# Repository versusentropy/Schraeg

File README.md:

# Schräg

Schräg is an 8HP multimode filter module for the eurorack format, based off the [Bastl Cinnamon](https://bastl-instruments.com/eurorack/modules/cinnamon).

## Smaller Warning and Disclaimer

As of 2021-03-01, at least one person has reported successfully building the current board revision. However, another builder reported a minor issue with the attenuverter circuits which prevents full-range voltage control over resonance (and limits voltage control over FM). This should be fixable only with component substitutions, we’re working on a fix. More information and updates [in the corresponding lines thread](https://llllllll.co/t/diy-module-release-schrag-bastl-cinnamon-rework/40590).

See the Changelog below for more updates and version-specific fixes.

## Quick links

* [Schematic](Schraeg/Schraeg.pdf)
* [Gerbers](Schraeg/output)
* [BOM](Schraeg/Schraeg%20BOM.csv)
* [Schräg on ModularGrid](https://www.modulargrid.net/e/other-unknown-schraeg)

## Features

Schräg is effectively a repackaged Bastl Cinnamon:

* Multimode filter with independent outputs (2-pole LP, 2-pole HP, 1-pole BP)
* V/oct input
* Self-resonates for use as a sine oscillator
* Input with an attenuator and 5x gain switch
* Two character switches for altering the resonance tracking
* All-SMD construction in a DIY-friendly format, with 0603 handsoldering footprints, all components on the back of the circuit board
* Built mostly using standard and easily-available components

with a few modifications:

* larger 8HP form factor, allowing for a big juicy cutoff knob and larger character and gain switches
* Voltage control over resonance, through an attenuverter
* FM input through an attenuverter, which works as a pitch fine-tune control with nothing patched
* A bi-directional power connector, with polyfuses
* An Interactive BOM (`Schraeg/Output/Interactive BOM.html` once you’ve cloned the repo locally) to aid in part placement
* Schematics and PCB laid out using KiCAD

The additional functionality is achieved with a minimum of extra components, thanks to the two unused VCA cells in the original design.

## License

The schematic, board layout and graphics are released under a cc-by-sa license. [Bastl Instruments](https://bastl-instruments.com/) generously gave their permission for me to release my rework of their module. They’re a cool company. Go check out their work!

## Development

In 2019 I was looking through the [Bastl Cinnamon schematic](https://github.com/bastl-instruments/bastlSchematics/blob/master/CINNAMON_V1.2.pdf) and realised that it only uses two of the four available V2164D VCA cells.

At the time I needed PCB layout practise (and a filter module for my DIY eurorack!), so I ended up prototyping and building an 8HP version of cinnamon for myself which uses the two spare cells to implement voltage control over resonance, as well as a few other little additions listed above.

I called it “Schräg” because of both the angled panel design, the weird sounds possible with Bastl’s cool distortion circuits, and the strange way KiCAD mangled the panel graphics.

A bit more than a year after building the first Schräg, I finally got around to fixing the various small issues with the first board revision, and asking Bastl if they were okay with me open-sourcing the project. They were, and here we are.

## Changelog

### v0.2.2

* Fixed attenuverter circuits (versusentroppy)
* Removed panel
* Added part numbers for JLCPCB
* Added placeholder for JLC's order number

### v0.2.1

* Fixed the LM4040 schematic symbols and PCB traces (#2)

### v0.2

* First version released to the public.
* These boards have an issue with the LM4040 orientation (see #2). Depending on the specific LM4040s, it may not cause any problems, but if building from scratch it’s best to install them correctly the first time. To fix it, solder the LM4040s at an angle so that pin 2 (NC) gets connected to pin 3 (5V Ref or GND, depending on the LM4040)

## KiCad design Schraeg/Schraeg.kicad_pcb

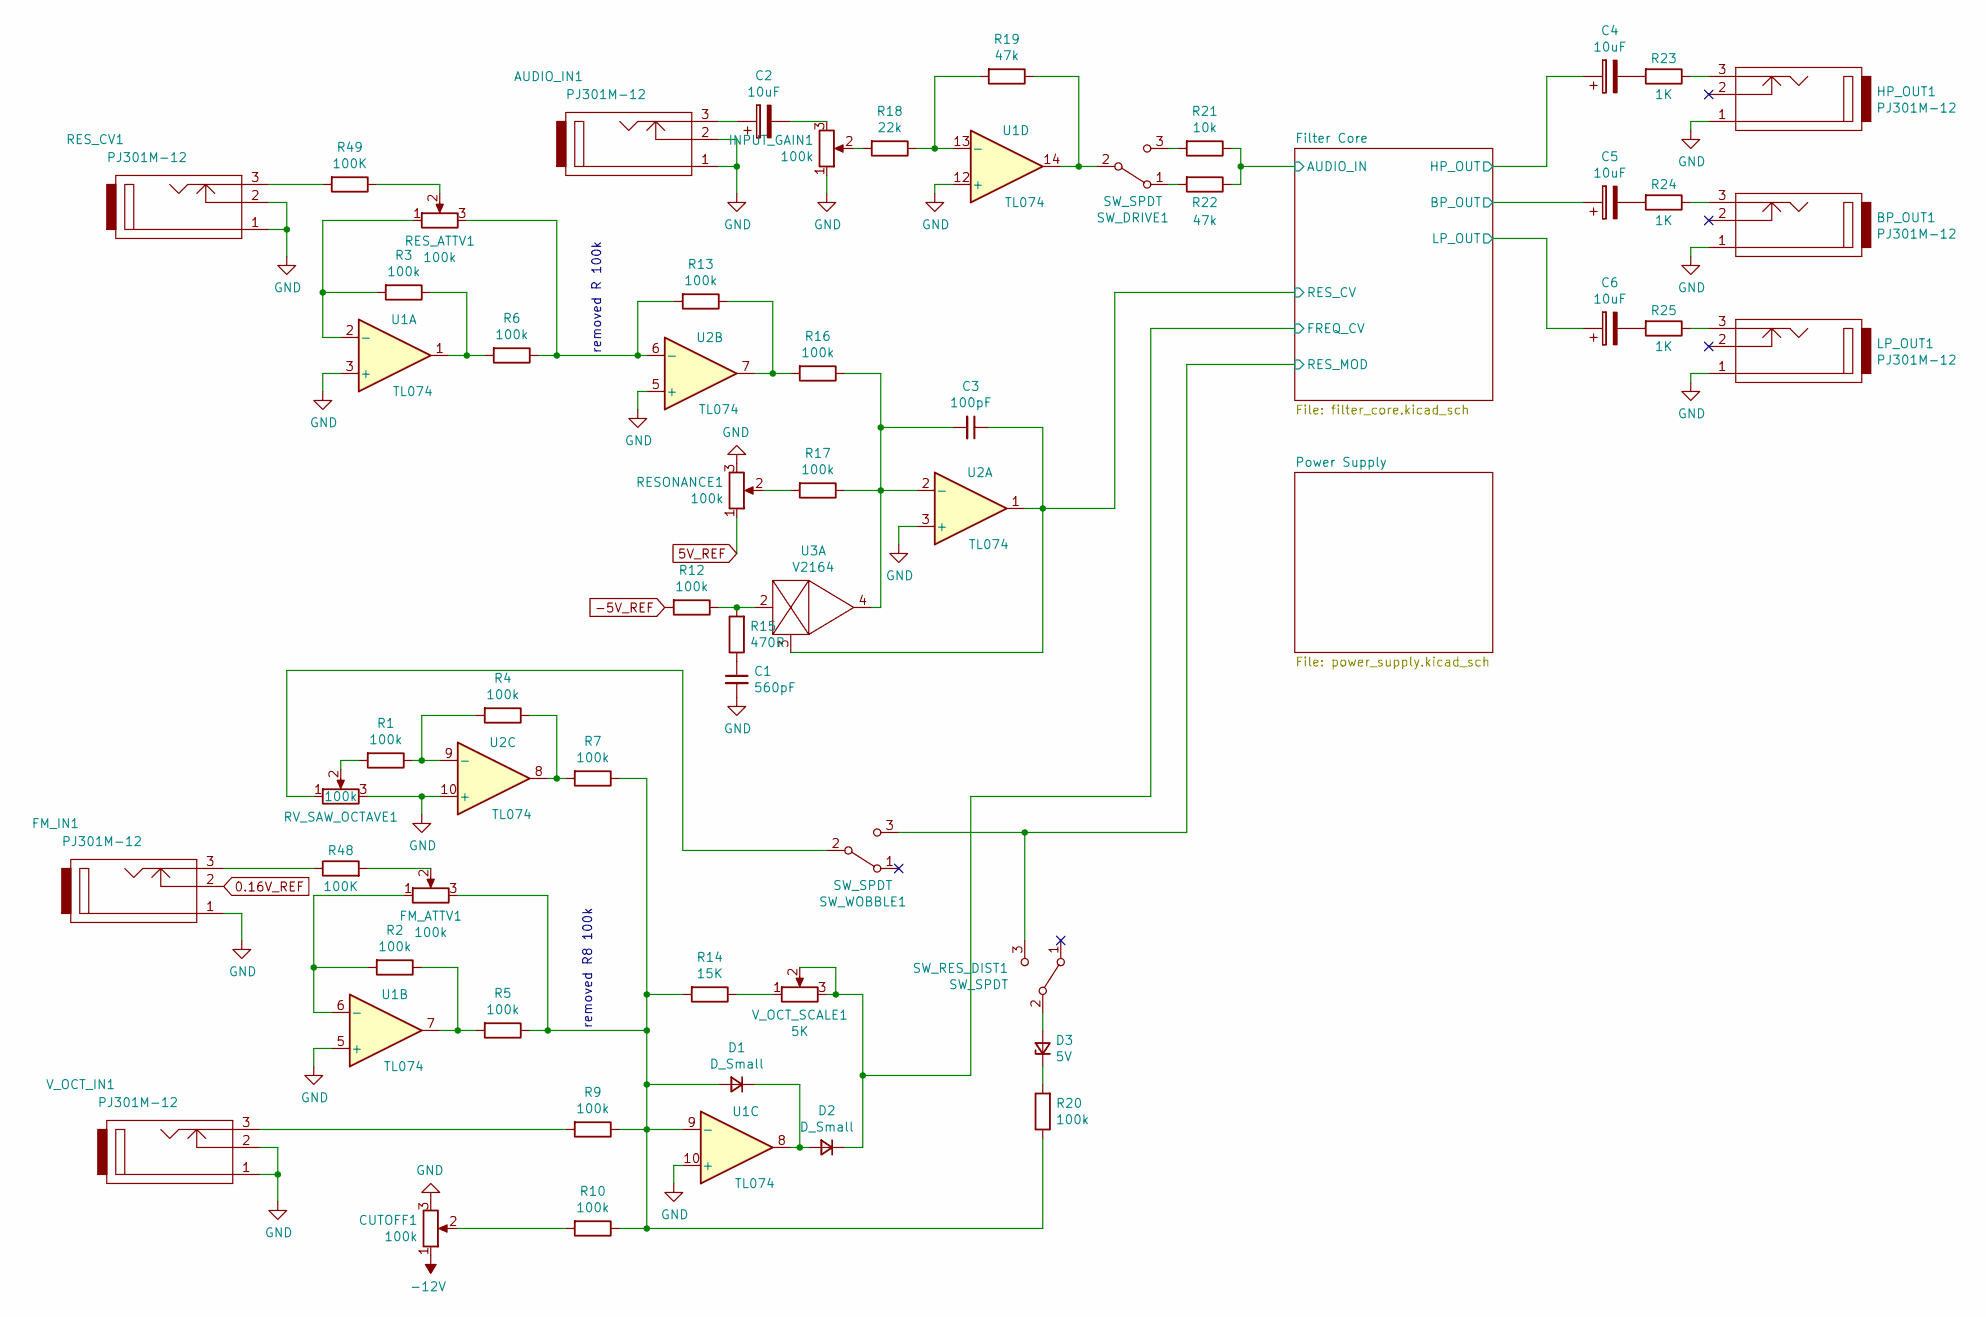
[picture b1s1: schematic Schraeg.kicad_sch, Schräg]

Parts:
AUDIO_IN1: PJ301M-12
BP_OUT1: PJ301M-12
C1: 560pF; C_0603_1608Metric_Pad1.05x0.95mm_HandSolder; LCSC C55393
C2, C4, C5, C6: 10uF; CP_Elec_5x4.5; Mouser 647-UCQ1V100MCL1GB
C3: 100pF; C_0603_1608Metric_Pad1.05x0.95mm_HandSolder; LCSC C14858
CUTOFF1: 100k; Alpha9mmPot
D1, D2: D_Small; D_SOD-123; LCSC C117948
D3: 5V; D_SOD-123; LCSC C173407
FM_ATTV1: 100k; Alpha9mmPot
FM_IN1: PJ301M-12
HP_OUT1: PJ301M-12
INPUT_GAIN1: 100k; Alpha9mmPot
LP_OUT1: PJ301M-12
R1, R2, R3, R4, R5, R6, R7, R9, R10, R12, R13, R16, R17, R20: 100k; R_0603_1608Metric_Pad1.05x0.95mm_HandSolder; LCSC C25803
R14: 15K; R_0603_1608Metric_Pad1.05x0.95mm_HandSolder; LCSC C22809
R15: 470R; R_0603_1608Metric_Pad1.05x0.95mm_HandSolder; LCSC C23179
R18: 22k; R_0603_1608Metric_Pad1.05x0.95mm_HandSolder; LCSC C31850
R19, R22: 47k; R_0603_1608Metric_Pad1.05x0.95mm_HandSolder; LCSC C25819
R21: 10k; R_0603_1608Metric_Pad1.05x0.95mm_HandSolder; LCSC C25804
R23, R24, R25: 1K; R_0603_1608Metric_Pad1.05x0.95mm_HandSolder; LCSC C21190
R48, R49: 100K; R_0603_1608Metric_Pad1.05x0.95mm_HandSolder; LCSC C25803
RESONANCE1: 100k; Alpha9mmPot
RES_ATTV1: 100k; Alpha9mmPot
RES_CV1: PJ301M-12
RV_SAW_OCTAVE1: 100k; Potentiometer_Bourns_3296W_Vertical
SW_DRIVE1: SW_SPDT; PinHeader_1x03_P2.54mm_Vertical
SW_RES_DIST1: SW_SPDT; PinHeader_1x03_P2.54mm_Vertical
SW_WOBBLE1: SW_SPDT; PinHeader_1x03_P2.54mm_Vertical
U1, U2: TL074; SOIC-14_3.9x8.7mm_P1.27mm; LCSC C12594
U3: V2164; SOIC-16_3.9x9.9mm_P1.27mm
V_OCT_IN1: PJ301M-12
V_OCT_SCALE1: 5K; Potentiometer_Bourns_3296W_Vertical

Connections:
0.16V_REF: FM_IN1.2; also elsewhere on the board
5V_REF: RESONANCE1.1; also elsewhere on the board
-5V_REF: R12.2; also elsewhere on the board
-12V: CUTOFF1.1; also elsewhere on the board
/Filter Core/AUDIO_IN: R21.1, R22.1; also elsewhere on the board
/Filter Core/BP_OUT: C5.1; also elsewhere on the board
/Filter Core/FREQ_CV: D2.1 (K), V_OCT_SCALE1.2, V_OCT_SCALE1.3; also elsewhere on the board
/Filter Core/HP_OUT: C4.1; also elsewhere on the board
/Filter Core/LP_OUT: C6.1; also elsewhere on the board
/Filter Core/RES_CV: C3.1, U2.1, U3.3; also elsewhere on the board
/Filter Core/RES_MOD: SW_RES_DIST1.3 (C), SW_WOBBLE1.3 (C); also elsewhere on the board
GND: AUDIO_IN1.1, AUDIO_IN1.2, BP_OUT1.1, C1.2, CUTOFF1.3, FM_IN1.1, HP_OUT1.1, INPUT_GAIN1.1, LP_OUT1.1, RESONANCE1.3, RES_CV1.1, RES_CV1.2, RV_SAW_OCTAVE1.3, U1.3 (+), U1.5 (+), U1.10 (+), U1.12 (+), U2.3 (+), U2.5 (+), U2.10 (+), V_OCT_IN1.1, V_OCT_IN1.2; also elsewhere on the board
unnamed: AUDIO_IN1.3, C2.1
unnamed: BP_OUT1.3, R24.1
unnamed: C1.1, R15.1
unnamed: C2.2, INPUT_GAIN1.3
unnamed: C3.2, R16.1, R17.1, U2.2 (-), U3.4
unnamed: C4.2, R23.2
unnamed: C5.2, R24.2
unnamed: C6.2, R25.2
unnamed: CUTOFF1.2, R10.2
unnamed: D1.1 (K), D2.2 (A), U1.8
unnamed: D1.2 (A), FM_ATTV1.3, R5.1, R7.1, R9.1, R10.1, R14.2, R20.1, U1.9 (-)
unnamed: D3.1 (K), R20.2
unnamed: D3.2 (A), SW_RES_DIST1.2 (B)
unnamed: FM_ATTV1.1, R2.2, U1.6 (-)
unnamed: FM_ATTV1.2, R48.2
unnamed: FM_IN1.3, R48.1
unnamed: HP_OUT1.3, R23.1
unnamed: INPUT_GAIN1.2, R18.2
unnamed: LP_OUT1.3, R25.1
unnamed: R1.1, R4.2, U2.9 (-)
unnamed: R1.2, RV_SAW_OCTAVE1.2
unnamed: R2.1, R5.2, U1.7
unnamed: R3.1, R6.2, U1.1
unnamed: R3.2, RES_ATTV1.1, U1.2 (-)
unnamed: R4.1, R7.2, U2.8
unnamed: R9.2, V_OCT_IN1.3
unnamed: R12.1, R15.2, U3.2
unnamed: R13.1, R16.2, U2.7
unnamed: R6.1, R13.2, RES_ATTV1.3, U2.6 (-)
unnamed: R14.1, V_OCT_SCALE1.1
unnamed: R17.2, RESONANCE1.2
unnamed: R18.1, R19.2, U1.13 (-)
unnamed: R19.1, SW_DRIVE1.2 (B), U1.14
unnamed: R21.2, SW_DRIVE1.3 (C)
unnamed: R22.2, SW_DRIVE1.1 (A)
unnamed: R49.1, RES_ATTV1.2
unnamed: R49.2, RES_CV1.3
unnamed: RV_SAW_OCTAVE1.1, SW_WOBBLE1.2 (B)

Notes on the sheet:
removed R8 100k
removed R 100k

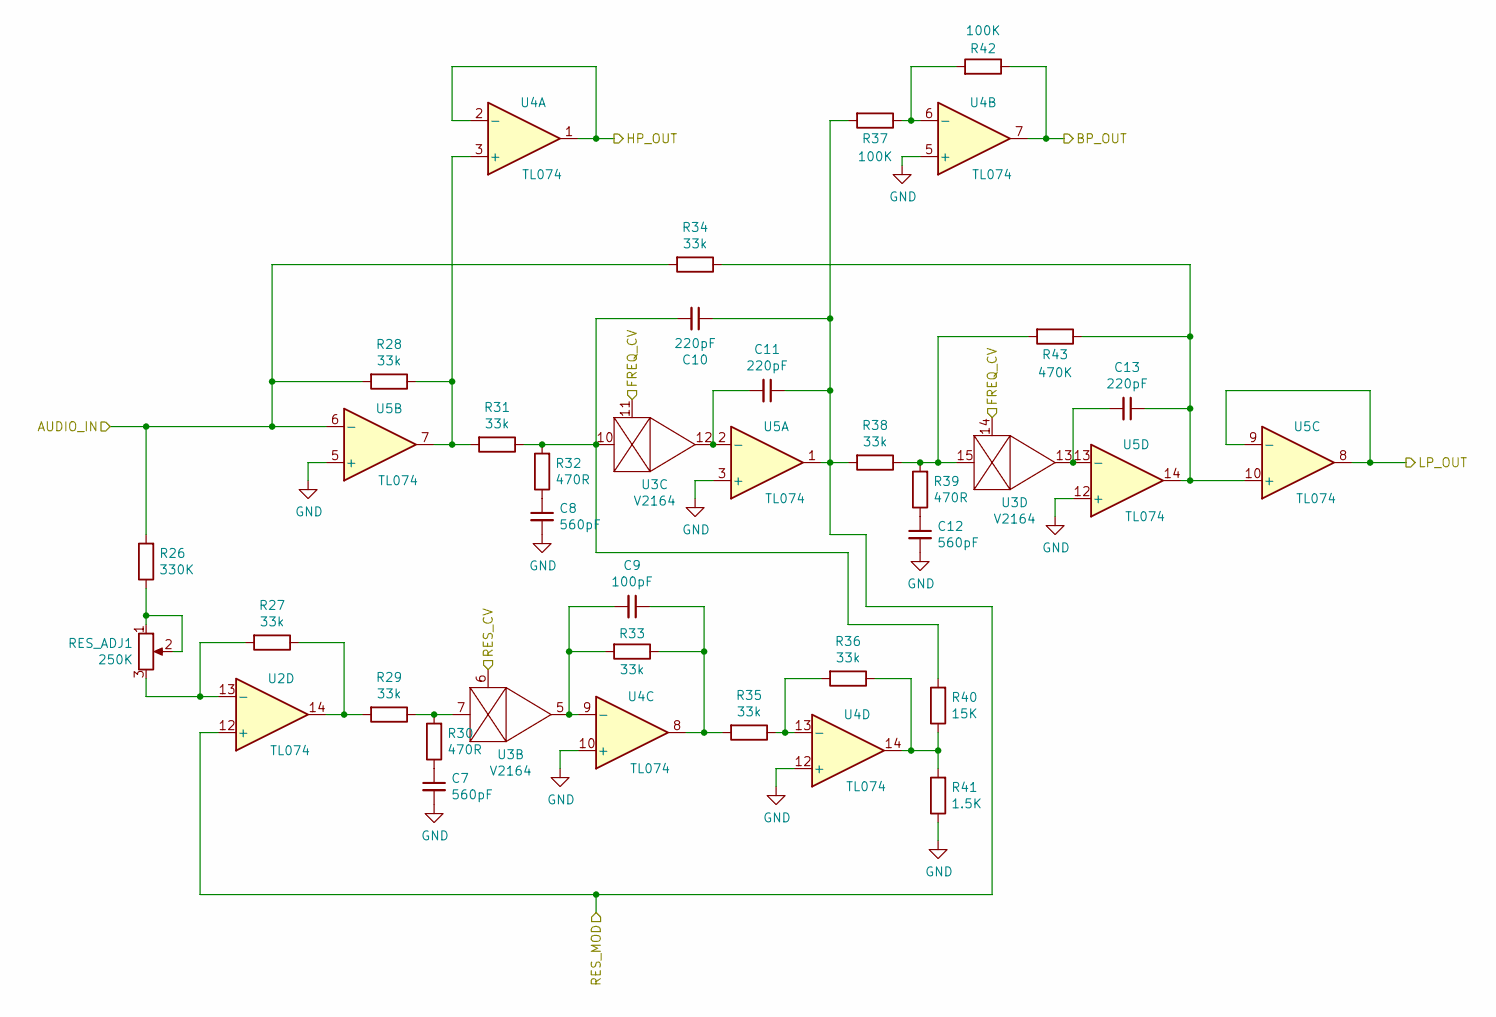
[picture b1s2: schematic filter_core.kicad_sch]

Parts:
C7, C8, C12: 560pF; C_0603_1608Metric_Pad1.05x0.95mm_HandSolder; LCSC C55393
C9: 100pF; C_0603_1608Metric_Pad1.05x0.95mm_HandSolder; LCSC C14858
C10, C11, C13: 220pF; C_0603_1608Metric_Pad1.05x0.95mm_HandSolder; LCSC C27675
R26: 330K; R_0603_1608Metric_Pad1.05x0.95mm_HandSolder; LCSC C23137
R27, R28, R29, R31, R33, R34, R35, R36, R38: 33k; R_0603_1608Metric_Pad1.05x0.95mm_HandSolder; LCSC C4216
R30, R32, R39: 470R; R_0603_1608Metric_Pad1.05x0.95mm_HandSolder; LCSC C23179
R37, R42: 100K; R_0603_1608Metric_Pad1.05x0.95mm_HandSolder; LCSC C25803
R40: 15K; R_0603_1608Metric_Pad1.05x0.95mm_HandSolder; LCSC C22809
R41: 1.5K; R_0603_1608Metric_Pad1.05x0.95mm_HandSolder; LCSC C22843
R43: 470K; R_0603_1608Metric_Pad1.05x0.95mm_HandSolder; LCSC C23178
RES_ADJ1: 250K; Potentiometer_Bourns_3296W_Vertical
U2, U4, U5: TL074; SOIC-14_3.9x8.7mm_P1.27mm; LCSC C12594
U3: V2164; SOIC-16_3.9x9.9mm_P1.27mm

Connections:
/Filter Core/AUDIO_IN: R26.2, R28.2, R34.2, U5.6 (-); also elsewhere on the board
/Filter Core/BP_OUT: R42.1, U4.7; also elsewhere on the board
/Filter Core/FREQ_CV: U3.11, U3.14; also elsewhere on the board
/Filter Core/HP_OUT: U4.1, U4.2 (-); also elsewhere on the board
/Filter Core/LP_OUT: U5.8, U5.9 (-); also elsewhere on the board
/Filter Core/RES_CV: U3.6; also elsewhere on the board
/Filter Core/RES_MOD: C10.1, C11.1, R37.2, R38.2, U2.12 (+), U5.1; also elsewhere on the board
GND: C7.2, C8.2, C12.2, R41.1, U4.5 (+), U4.10 (+), U4.12 (+), U5.3 (+), U5.5 (+), U5.12 (+); also elsewhere on the board
unnamed: C7.1, R30.1
unnamed: C8.1, R32.1
unnamed: C9.1, R33.1, R35.2, U4.8
unnamed: C9.2, R33.2, U3.5, U4.9 (-)
unnamed: C10.2, R31.1, R32.2, R40.2, U3.10
unnamed: C11.2, U3.12, U5.2 (-)
unnamed: C12.1, R39.1
unnamed: C13.1, R34.1, R43.1, U5.10 (+), U5.14
unnamed: C13.2, U3.13, U5.13 (-)
unnamed: R26.1, RES_ADJ1.1, RES_ADJ1.2
unnamed: R27.1, R29.2, U2.14
unnamed: R27.2, RES_ADJ1.3, U2.13 (-)
unnamed: R28.1, R31.2, U4.3 (+), U5.7
unnamed: R29.1, R30.2, U3.7
unnamed: R35.1, R36.2, U4.13 (-)
unnamed: R36.1, R40.1, R41.2, U4.14
unnamed: R37.1, R42.2, U4.6 (-)
unnamed: R38.1, R39.2, R43.2, U3.15

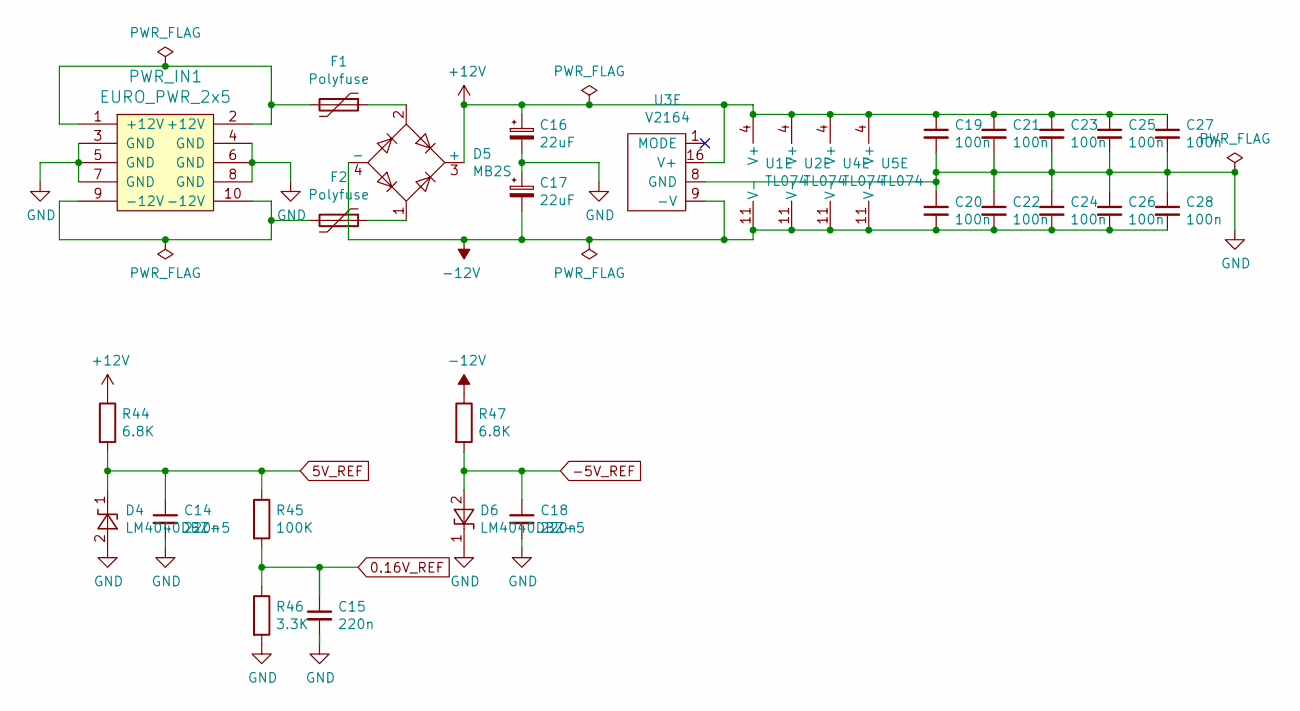
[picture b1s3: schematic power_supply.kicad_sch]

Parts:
C14, C15, C18: 220n; C_0603_1608Metric_Pad1.05x0.95mm_HandSolder; LCSC C21120
C16, C17: 22uF; CP_Elec_6.3x5.4; LCSC C72505
C19, C20, C21, C22, C23, C24, C25, C26, C27, C28: 100n; C_0603_1608Metric_Pad1.05x0.95mm_HandSolder; LCSC C14663
D4, D6: LM4040DBZ-5; SOT-23; LCSC C202168
D5: MB2S; TO-269AA; Mouser 625-MB2S-E3/80
F1, F2: Polyfuse; Fuse_1206_3216Metric_Pad1.42x1.75mm_HandSolder; LCSC C261946
PWR_IN1: EURO_PWR_2x5; PinHeader_2x05_P2.54mm_Vertical
R44, R47: 6.8K; R_0603_1608Metric_Pad1.05x0.95mm_HandSolder; LCSC C23212
R45: 100K; R_0603_1608Metric_Pad1.05x0.95mm_HandSolder; LCSC C25803
R46: 3.3K; R_0603_1608Metric_Pad1.05x0.95mm_HandSolder; LCSC C22978
U1, U2, U4, U5: TL074; SOIC-14_3.9x8.7mm_P1.27mm; LCSC C12594
U3: V2164; SOIC-16_3.9x9.9mm_P1.27mm

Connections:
0.16V_REF: C15.1, R45.2, R46.1; also elsewhere on the board
5V_REF: C14.1, D4.1 (K), R44.2, R45.1; also elsewhere on the board
+12V: C16.1, C19.1, C21.1, C23.1, C25.1, C27.1, D5.3 (+), R44.1, U1.4 (V+), U2.4 (V+), U3.16 (V+), U4.4 (V+), U5.4 (V+)
-5V_REF: C18.1, D6.2 (A), R47.2; also elsewhere on the board
-12V: C17.2, C20.2, C22.2, C24.2, C26.2, C28.2, D5.4 (-), R47.1, U1.11 (V-), U2.11 (V-), U3.9 (-V), U4.11 (V-), U5.11 (V-); also elsewhere on the board
GND: C14.2, C15.2, C16.2, C17.1, C18.2, C19.2, C20.1, C21.2, C22.1, C23.2, C24.1, C25.2, C26.1, C27.2, C28.1, D4.2 (A), D6.1 (K), PWR_IN1.3 (GND), PWR_IN1.4 (GND), PWR_IN1.5 (GND), PWR_IN1.6 (GND), PWR_IN1.7 (GND), PWR_IN1.8 (GND), R46.2, U3.8 (GND); also elsewhere on the board
unnamed: D5.1, F2.1
unnamed: D5.2, F1.1
unnamed: F1.2, PWR_IN1.1 (+12V), PWR_IN1.2 (+12V)
unnamed: F2.2, PWR_IN1.9 (-12V), PWR_IN1.10 (-12V)

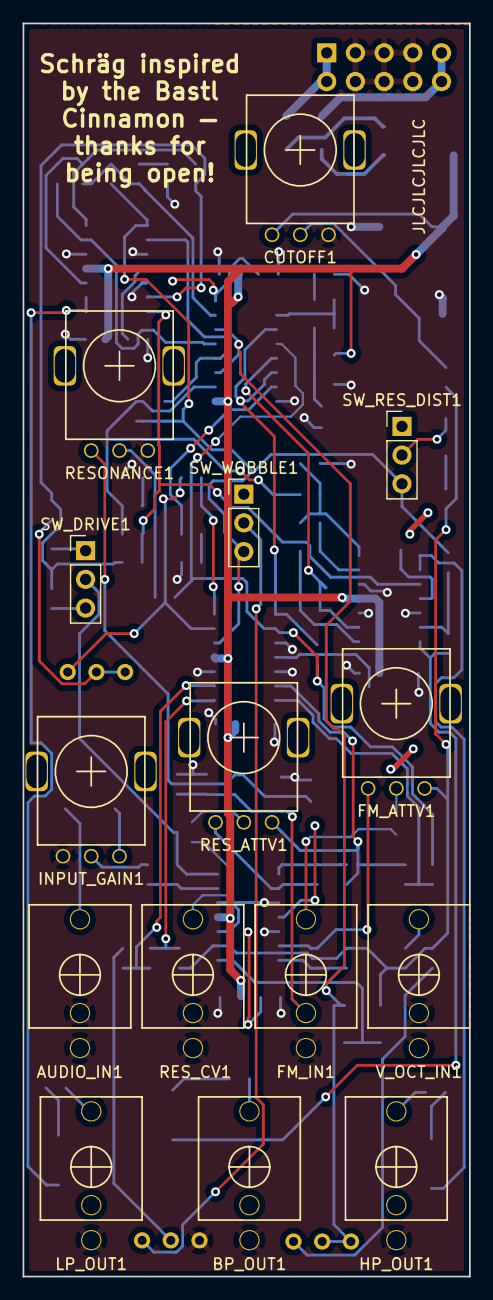
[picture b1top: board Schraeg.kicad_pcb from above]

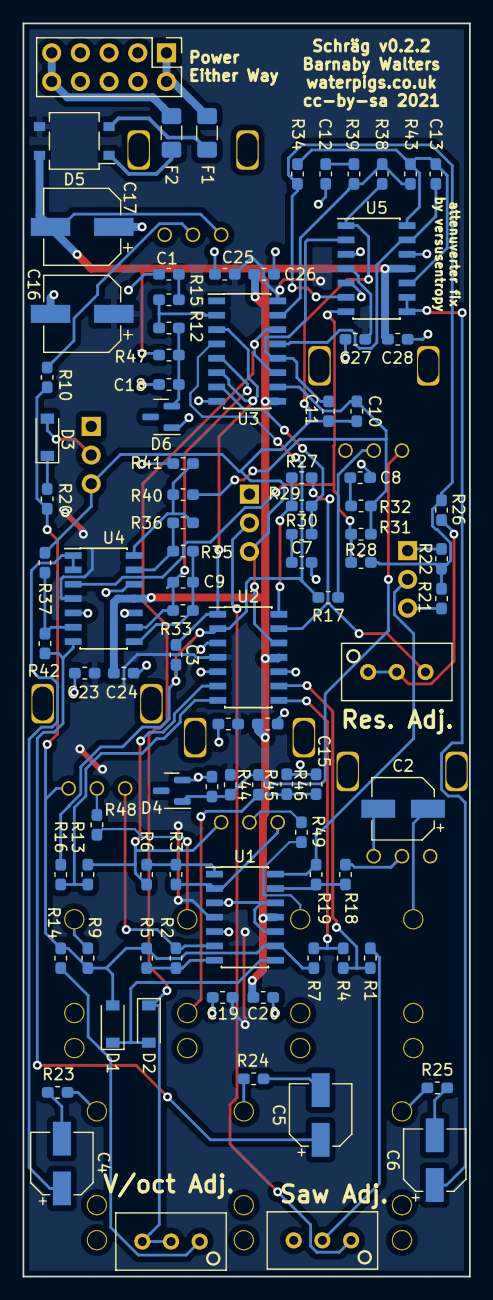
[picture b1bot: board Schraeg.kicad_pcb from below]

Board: 2 copper layers, 39.5 x 110.9 mm, 107 parts (92 on the bottom side), 73 nets.

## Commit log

2022-01-16 Add LCSC/Mouser BOM
2022-01-27 v0.2.2 BOM+POS+JLC placeholder
2022-02-05 gerber+bom

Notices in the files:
Schraeg/Schraeg.kicad_pcb:
cc-by-sa 2021
